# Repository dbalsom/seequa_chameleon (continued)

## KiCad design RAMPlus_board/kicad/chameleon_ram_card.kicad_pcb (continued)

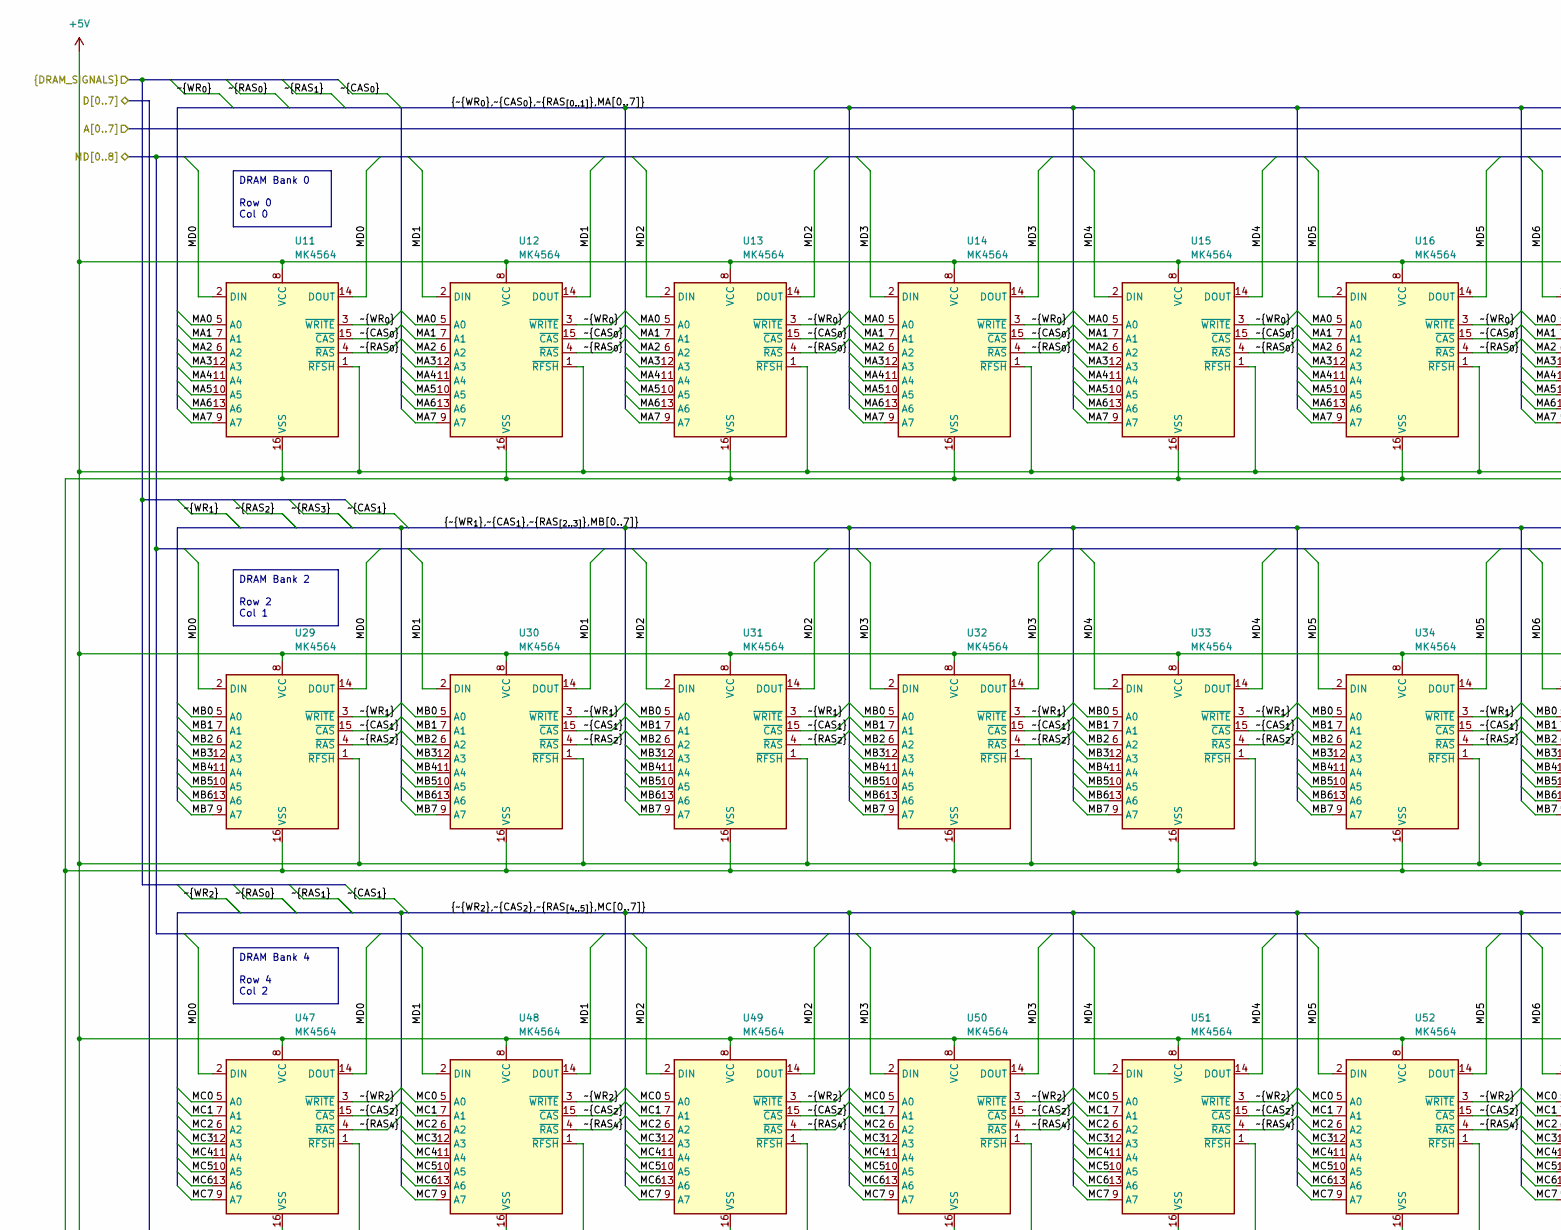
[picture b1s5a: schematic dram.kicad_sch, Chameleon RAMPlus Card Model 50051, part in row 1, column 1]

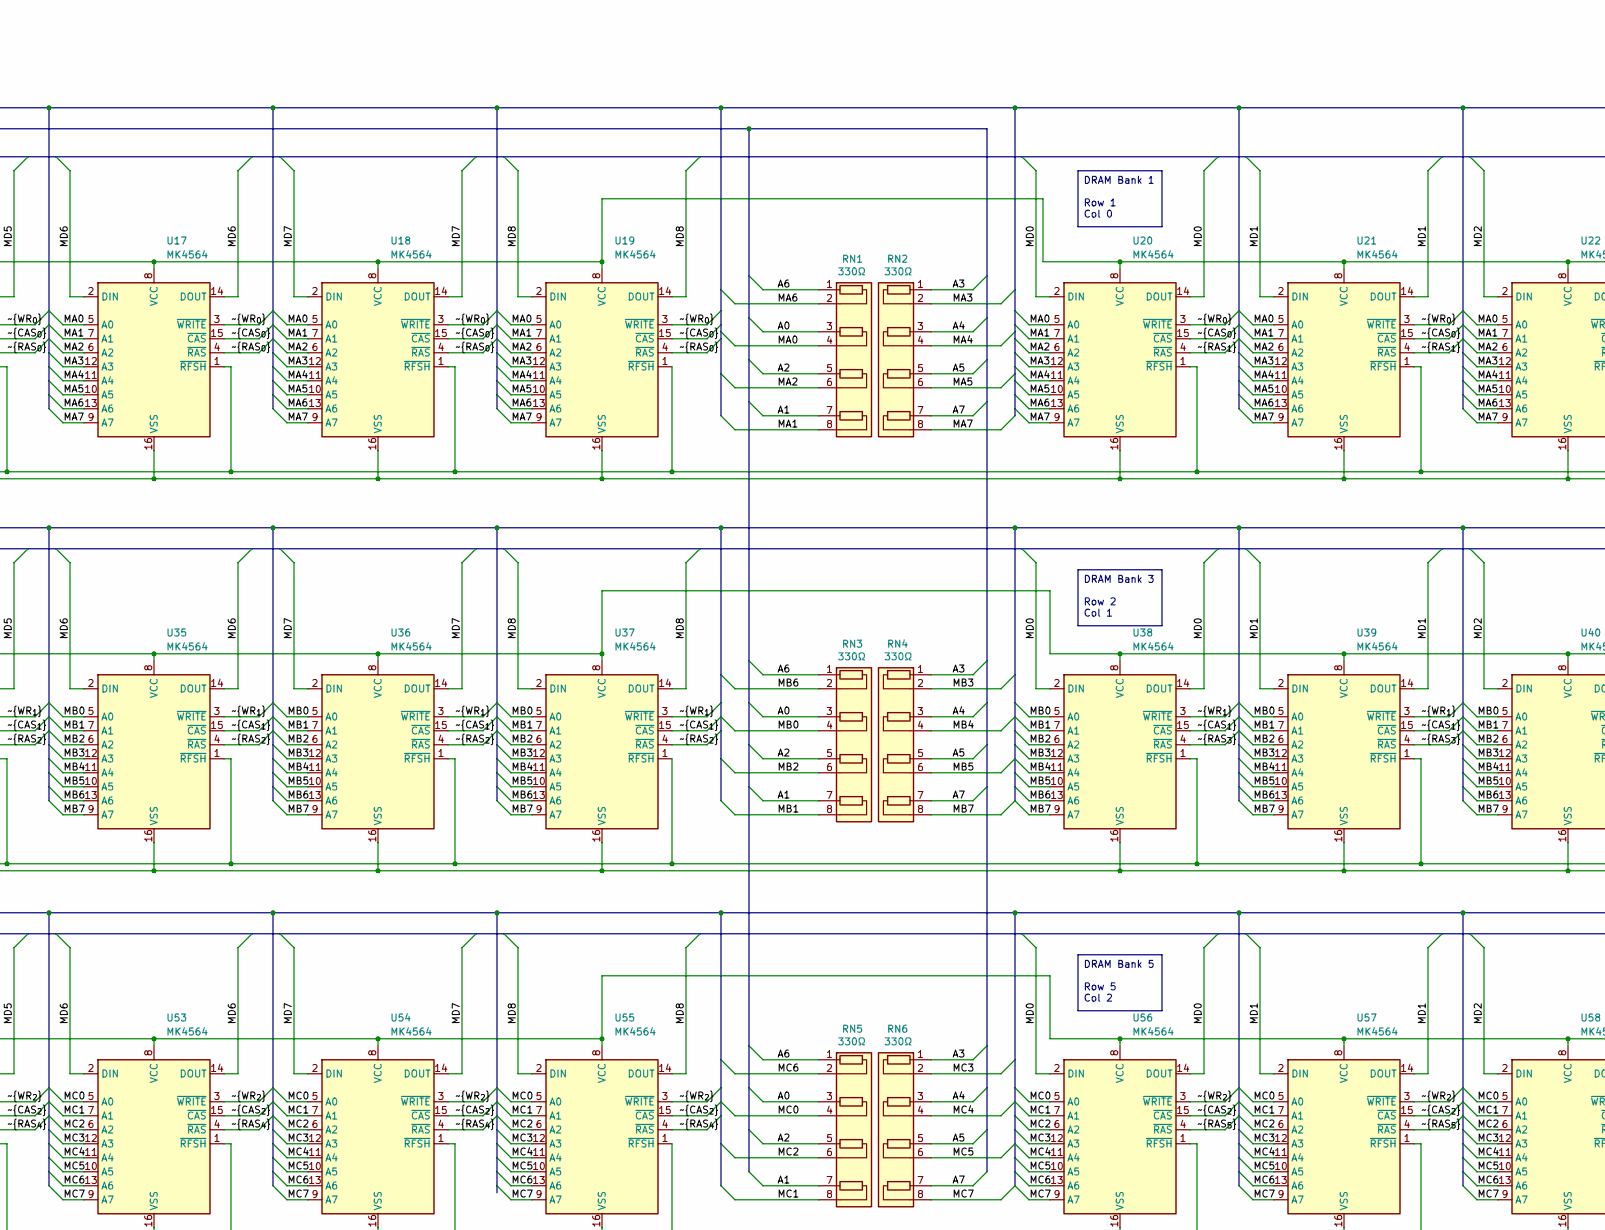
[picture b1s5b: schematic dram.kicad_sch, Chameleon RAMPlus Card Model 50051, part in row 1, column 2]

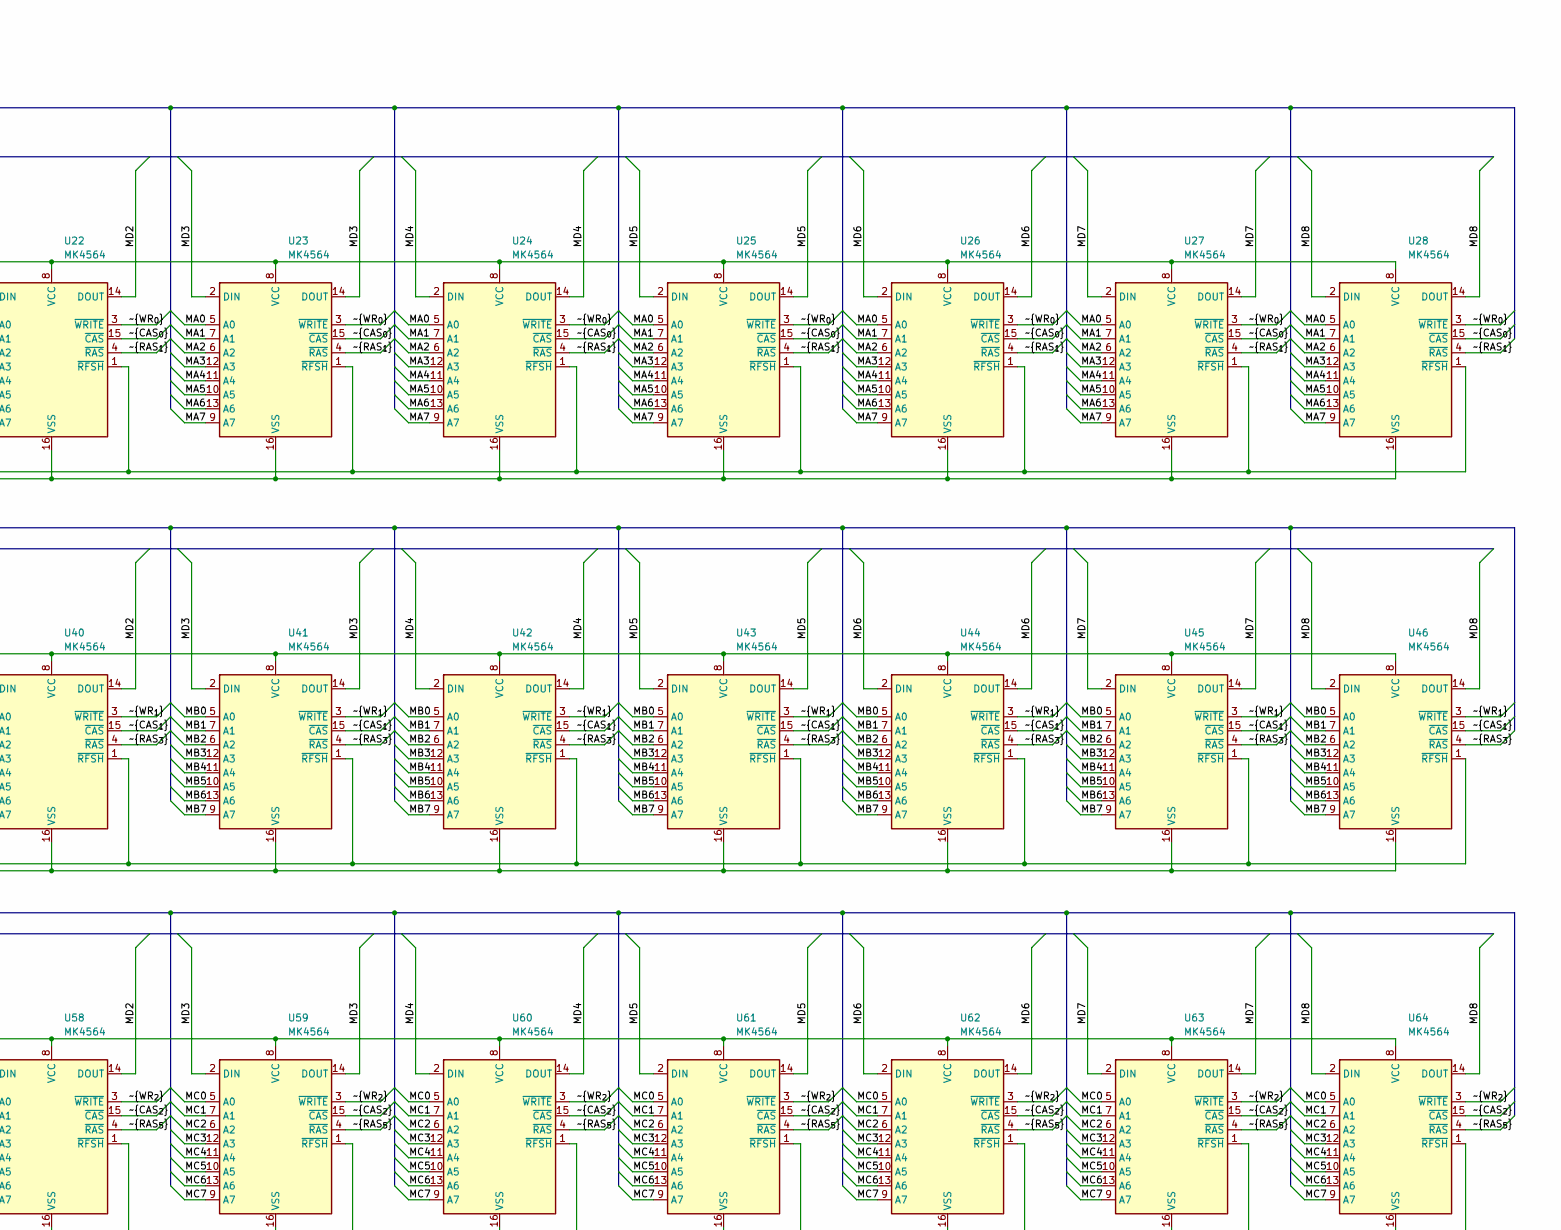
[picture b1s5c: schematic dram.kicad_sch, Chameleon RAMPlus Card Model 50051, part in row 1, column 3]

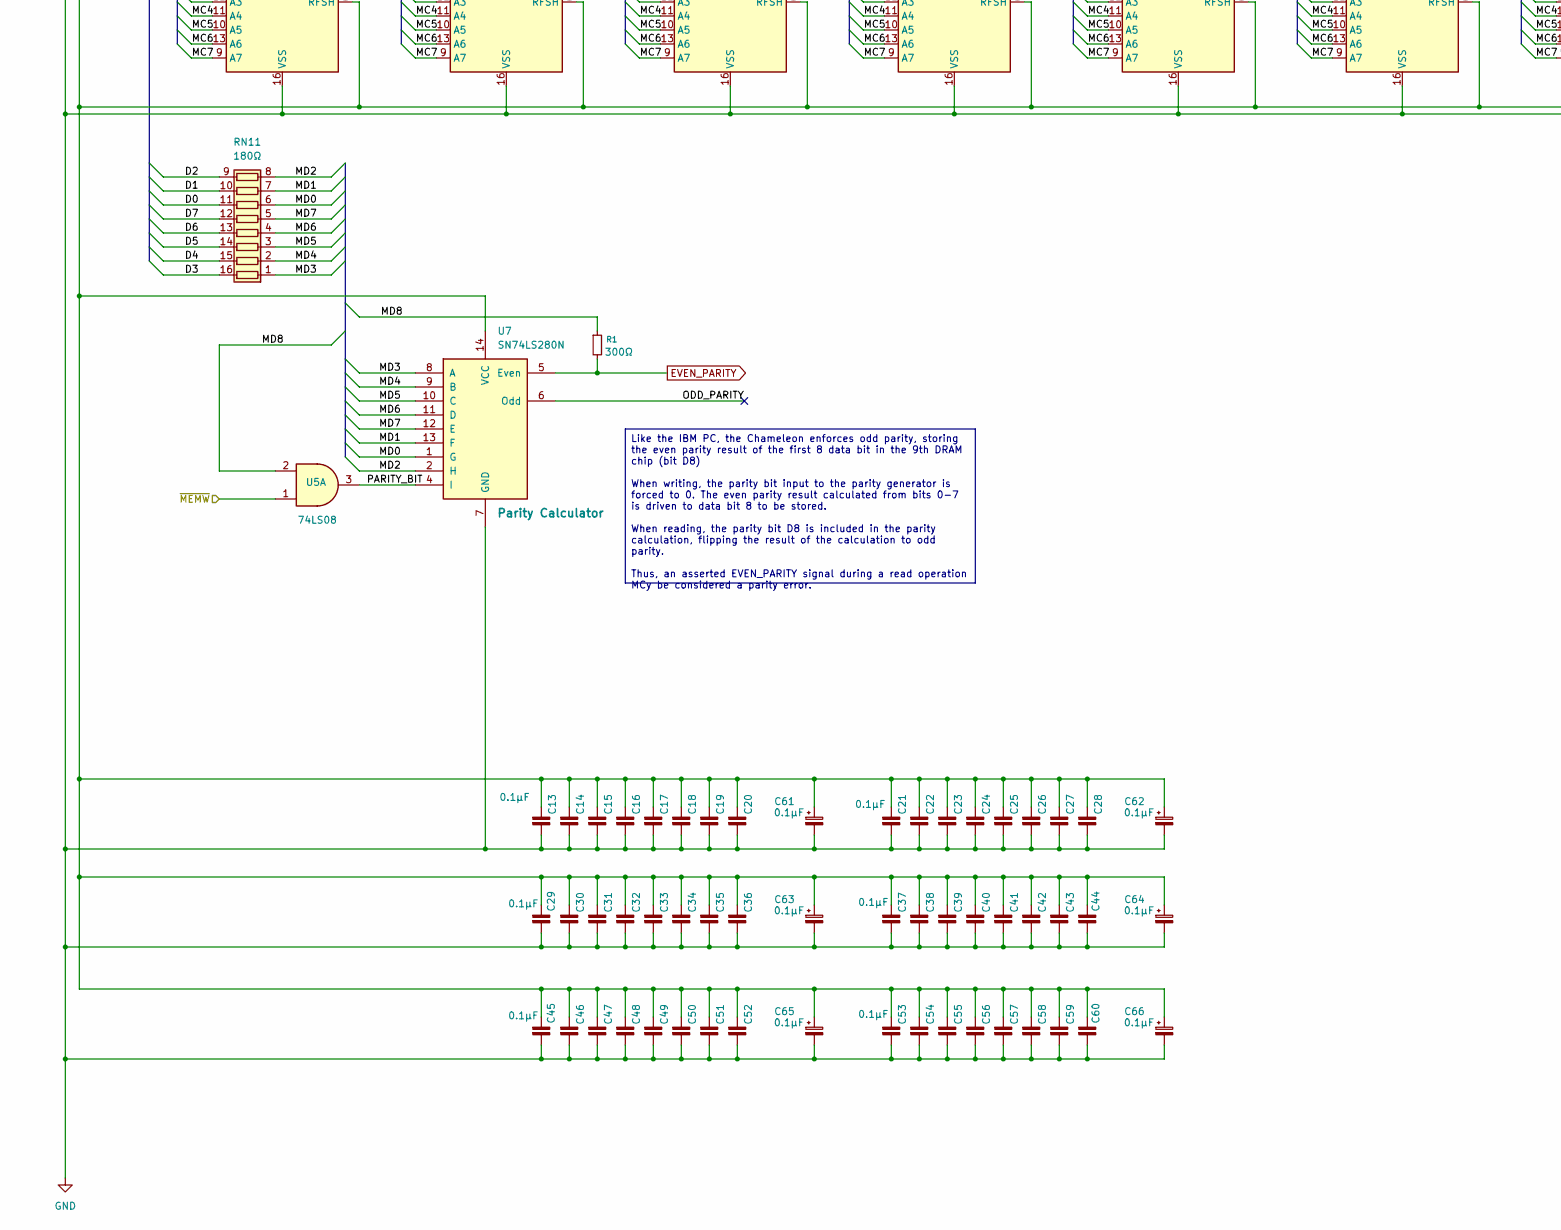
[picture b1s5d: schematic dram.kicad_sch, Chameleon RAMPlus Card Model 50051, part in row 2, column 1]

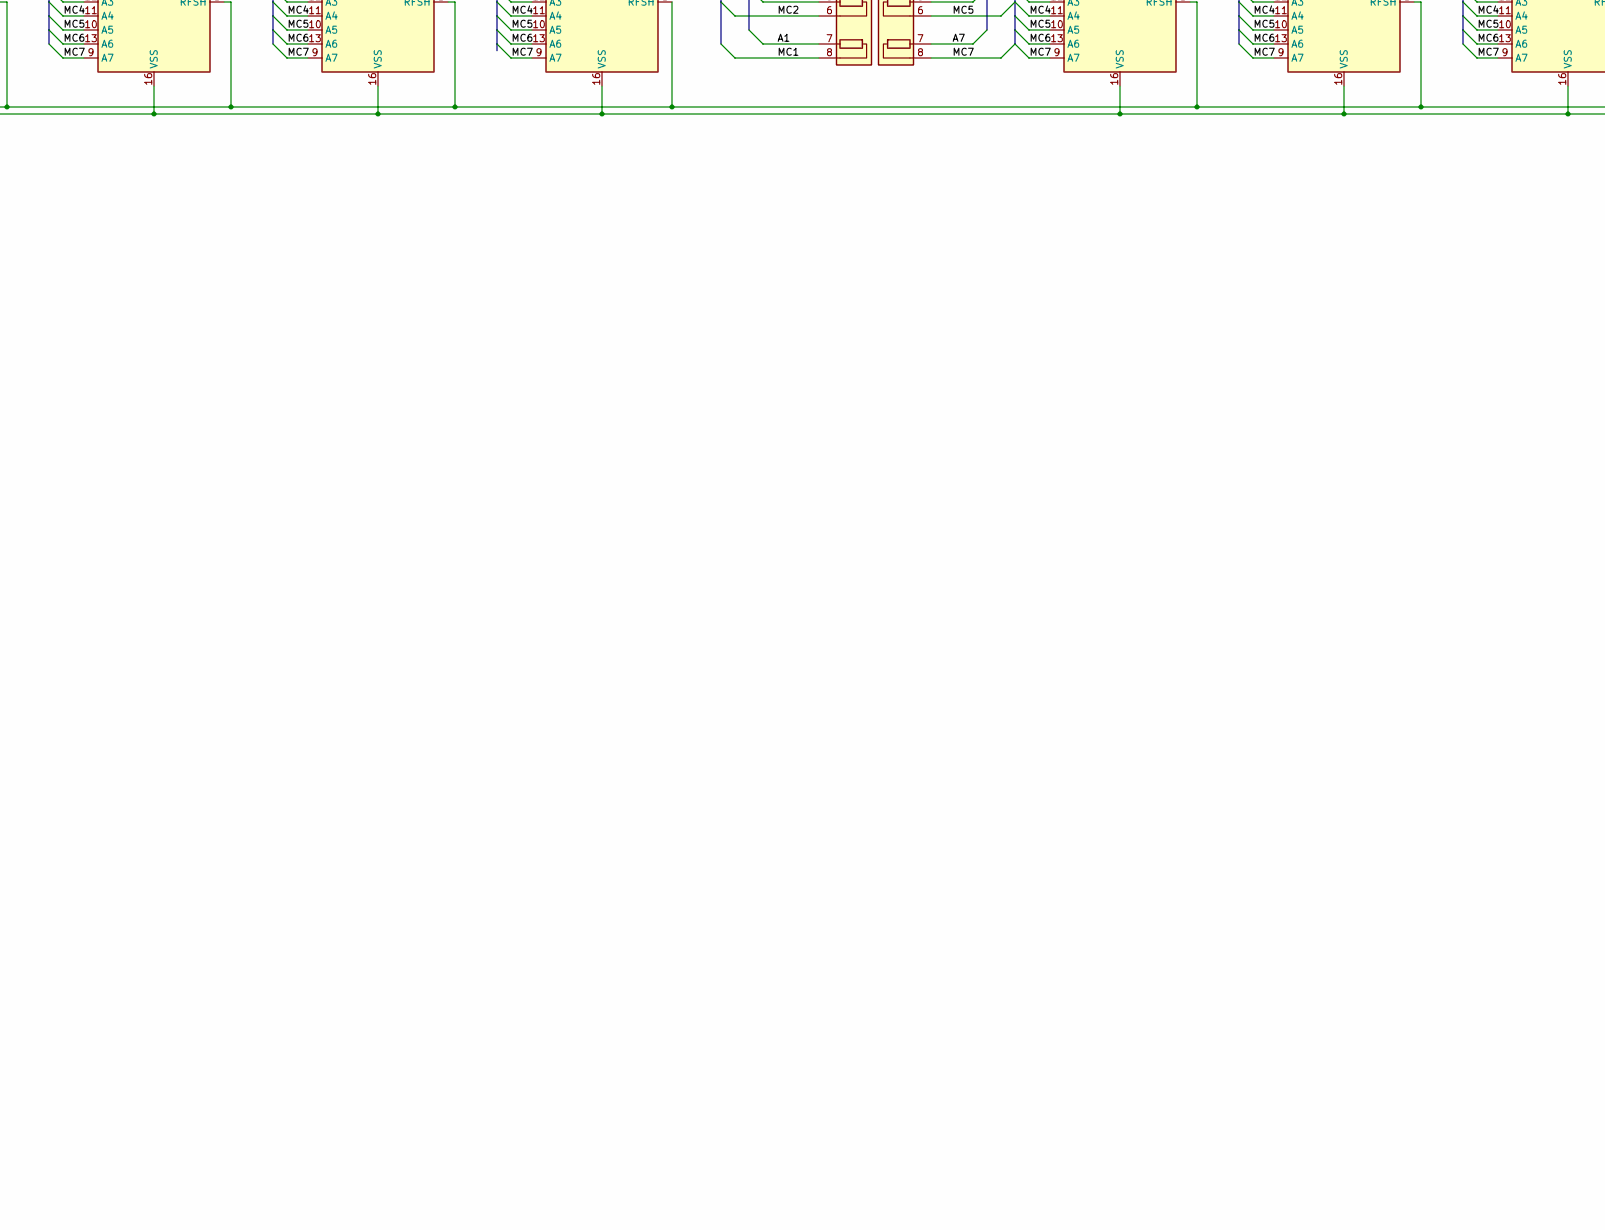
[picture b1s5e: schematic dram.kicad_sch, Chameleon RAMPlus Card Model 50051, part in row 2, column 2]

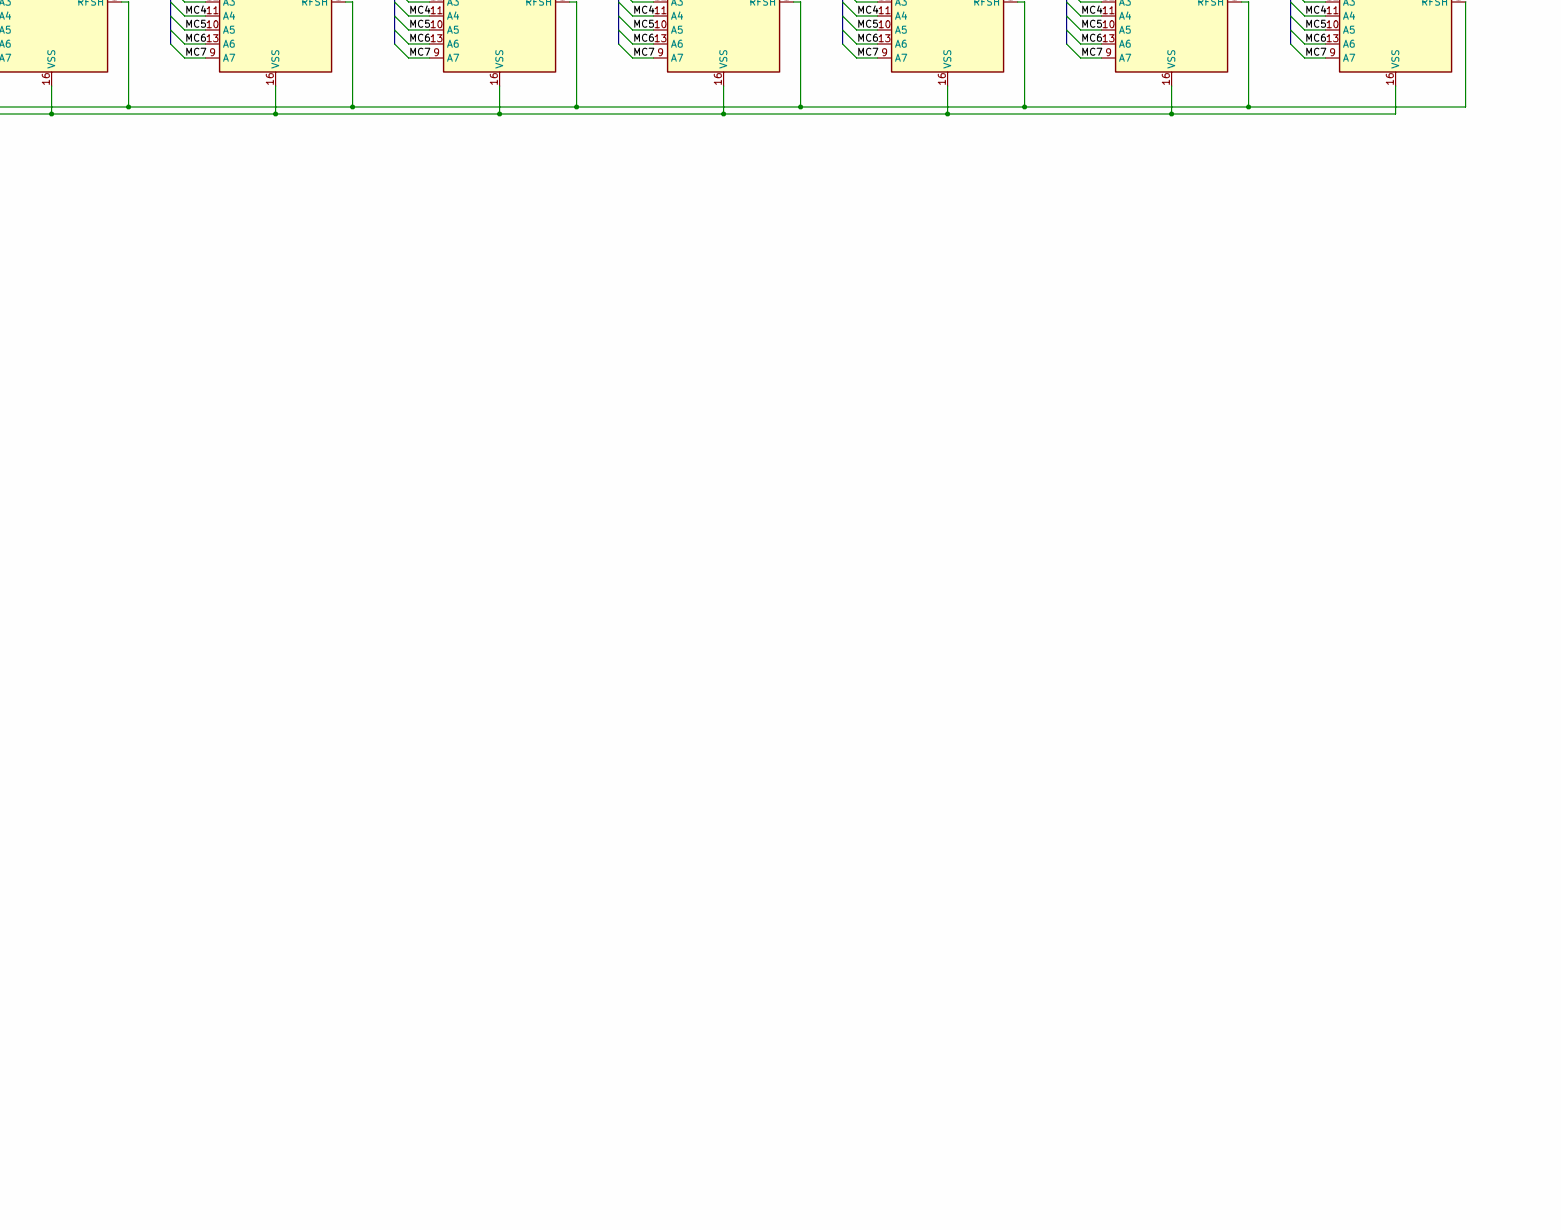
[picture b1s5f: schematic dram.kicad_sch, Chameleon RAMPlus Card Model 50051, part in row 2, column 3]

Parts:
C13, C28: 0.1µF; C_Seequa_MLCC_Bypass_P3.7mm
C14, C15, C16, C17, C18, C19, C20, C21, C22, C23, C24, C25, C26, C27, C29, C30, C31, C32, C33, C34, C35, C36, C38, C39, C40, C41, C42, C43, C44, C45, C46, C47, C48, C49, C50, C51, C52, C54, C55, C56, C57, C58, C59, C60: 0.1µF; C_Seequa_MLCC_Bypass_P7.62mm
C37, C53: 0.1µF; C_Seequa_MLCC_Bypass_P5mm
C61, C62, C63, C64, C65, C66: 0.1µF; C_Seequa_Bypass_2.54mm
R1: 300Ω; R_Seequa_P10_7.5mm_Box
RN1, RN2, RN3, RN4, RN5, RN6: 330Ω; R_Array_SIP8
RN11: 180Ω; DIP-16_W7.62mm_Socket
U5: 74LS08; DIP-14_W7.62mm_Socket
U7: SN74LS280N; DIP-14_W7.62mm_Socket
U11, U12, U13, U14, U15, U16, U17, U18, U19, U20, U21, U22, U23, U24, U25, U26, U27, U28, U29, U30, U31, U32, U33, U34, U35, U36, U37, U38, U39, U40, U41, U42, U43, U44, U45, U46, U47, U48, U49, U50, U51, U52, U53, U54, U55, U56, U57, U58, U59, U60, U61, U62, U63, U64: MK4564; DIP-16_W7.62mm_MK4164N_Socketed_With_Chip

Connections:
+5V: C13.1, C14.1, C15.1, C16.1, C17.1, C18.1, C19.1, C20.1, C21.1, C22.1, C23.1, C24.1, C25.1, C26.1, C27.1, C28.1, C29.1, C30.1, C31.1, C32.1, C33.1, C34.1, C35.1, C36.1, C37.1, C38.1, C39.1, C40.1, C41.1, C42.1, C43.1, C44.1, C45.1, C46.1, C47.1, C48.1, C49.1, C50.1, C51.1, C52.1, C53.1, C54.1, C55.1, C56.1, C57.1, C58.1, C59.1, C60.1, C61.1, C62.1, C63.1, C64.1, C65.1, C66.1, U7.14 (VCC), U11.1 (~RFSH), U11.8 (VCC), U12.1 (~RFSH), U12.8 (VCC), U13.1 (~RFSH), U13.8 (VCC), U14.1 (~RFSH), U14.8 (VCC), U15.1 (~RFSH), U15.8 (VCC), U16.1 (~RFSH), U16.8 (VCC), U17.1 (~RFSH), U17.8 (VCC), U18.1 (~RFSH), U18.8 (VCC), U19.1 (~RFSH), U19.8 (VCC), U20.1 (~RFSH), U20.8 (VCC), U21.1 (~RFSH), U21.8 (VCC), U22.1 (~RFSH), U22.8 (VCC), U23.1 (~RFSH), U23.8 (VCC), U24.1 (~RFSH), U24.8 (VCC), U25.1 (~RFSH), U25.8 (VCC), U26.1 (~RFSH), U26.8 (VCC), U27.1 (~RFSH), U27.8 (VCC), U28.1 (~RFSH), U28.8 (VCC), U29.1 (~RFSH), U29.8 (VCC), U30.1 (~RFSH), U30.8 (VCC), U31.1 (~RFSH), U31.8 (VCC), U32.1 (~RFSH), U32.8 (VCC), U33.1 (~RFSH), U33.8 (VCC), U34.1 (~RFSH), U34.8 (VCC), U35.1 (~RFSH), U35.8 (VCC), U36.1 (~RFSH), U36.8 (VCC), U37.1 (~RFSH), U37.8 (VCC), U38.1 (~RFSH), U38.8 (VCC), U39.1 (~RFSH), U39.8 (VCC), U40.1 (~RFSH), U40.8 (VCC), U41.1 (~RFSH), U41.8 (VCC), U42.1 (~RFSH), U42.8 (VCC), U43.1 (~RFSH), U43.8 (VCC), U44.1 (~RFSH), U44.8 (VCC), U45.1 (~RFSH), U45.8 (VCC), U46.1 (~RFSH), U46.8 (VCC), U47.1 (~RFSH), U47.8 (VCC), U48.1 (~RFSH), U48.8 (VCC), U49.1 (~RFSH), U49.8 (VCC), U50.1 (~RFSH), U50.8 (VCC), U51.1 (~RFSH), U51.8 (VCC), U52.1 (~RFSH), U52.8 (VCC), U53.1 (~RFSH), U53.8 (VCC), U54.1 (~RFSH), U54.8 (VCC), U55.1 (~RFSH), U55.8 (VCC), U56.1 (~RFSH), U56.8 (VCC), U57.1 (~RFSH), U57.8 (VCC), U58.1 (~RFSH), U58.8 (VCC), U59.1 (~RFSH), U59.8 (VCC), U60.1 (~RFSH), U60.8 (VCC), U61.1 (~RFSH), U61.8 (VCC), U62.1 (~RFSH), U62.8 (VCC), U63.1 (~RFSH), U63.8 (VCC), U64.1 (~RFSH), U64.8 (VCC); also elsewhere on the board
/Bus Interface & DRAM Controller/A0: RN1.3 (R2.1), RN3.3 (R2.1), RN5.3 (R2.1); also elsewhere on the board
/Bus Interface & DRAM Controller/A1: RN1.7 (R4.1), RN3.7 (R4.1), RN5.7 (R4.1); also elsewhere on the board
/Bus Interface & DRAM Controller/A2: RN1.5 (R3.1), RN3.5 (R3.1), RN5.5 (R3.1); also elsewhere on the board
/Bus Interface & DRAM Controller/A3: RN2.1 (R1.1), RN4.1 (R1.1), RN6.1 (R1.1); also elsewhere on the board
/Bus Interface & DRAM Controller/A4: RN2.3 (R2.1), RN4.3 (R2.1), RN6.3 (R2.1); also elsewhere on the board
/Bus Interface & DRAM Controller/A5: RN2.5 (R3.1), RN4.5 (R3.1), RN6.5 (R3.1); also elsewhere on the board
/Bus Interface & DRAM Controller/A6: RN1.1 (R1.1), RN3.1 (R1.1), RN5.1 (R1.1); also elsewhere on the board
/Bus Interface & DRAM Controller/A7: RN2.7 (R4.1), RN4.7 (R4.1), RN6.7 (R4.1); also elsewhere on the board
/Bus Interface & DRAM Controller/D0: RN11.11 (R6.2); also elsewhere on the board
/Bus Interface & DRAM Controller/D1: RN11.10 (R7.2); also elsewhere on the board
/Bus Interface & DRAM Controller/D2: RN11.9 (R8.2); also elsewhere on the board
/Bus Interface & DRAM Controller/D3: RN11.16 (R1.2); also elsewhere on the board
/Bus Interface & DRAM Controller/D4: RN11.15 (R2.2); also elsewhere on the board
/Bus Interface & DRAM Controller/D5: RN11.14 (R3.2); also elsewhere on the board
/Bus Interface & DRAM Controller/D6: RN11.13 (R4.2); also elsewhere on the board
/Bus Interface & DRAM Controller/D7: RN11.12 (R5.2); also elsewhere on the board
/Bus Interface & DRAM Controller/~CAS_{0}: U11.15 (~CAS), U12.15 (~CAS), U13.15 (~CAS), U14.15 (~CAS), U15.15 (~CAS), U16.15 (~CAS), U17.15 (~CAS), U18.15 (~CAS), U19.15 (~CAS), U20.15 (~CAS), U21.15 (~CAS), U22.15 (~CAS), U23.15 (~CAS), U24.15 (~CAS), U25.15 (~CAS), U26.15 (~CAS), U27.15 (~CAS), U28.15 (~CAS); also elsewhere on the board
/Bus Interface & DRAM Controller/~CAS_{1}: U29.15 (~CAS), U30.15 (~CAS), U31.15 (~CAS), U32.15 (~CAS), U33.15 (~CAS), U34.15 (~CAS), U35.15 (~CAS), U36.15 (~CAS), U37.15 (~CAS), U38.15 (~CAS), U39.15 (~CAS), U40.15 (~CAS), U41.15 (~CAS), U42.15 (~CAS), U43.15 (~CAS), U44.15 (~CAS), U45.15 (~CAS), U46.15 (~CAS); also elsewhere on the board
/Bus Interface & DRAM Controller/~CAS_{2}: U47.15 (~CAS), U48.15 (~CAS), U49.15 (~CAS), U50.15 (~CAS), U51.15 (~CAS), U52.15 (~CAS), U53.15 (~CAS), U54.15 (~CAS), U55.15 (~CAS), U56.15 (~CAS), U57.15 (~CAS), U58.15 (~CAS), U59.15 (~CAS), U60.15 (~CAS), U61.15 (~CAS), U62.15 (~CAS), U63.15 (~CAS), U64.15 (~CAS); also elsewhere on the board
/Bus Interface & DRAM Controller/~MEMW: U5.1; also elsewhere on the board
/Bus Interface & DRAM Controller/~RAS_{0}: U11.4 (~RAS), U12.4 (~RAS), U13.4 (~RAS), U14.4 (~RAS), U15.4 (~RAS), U16.4 (~RAS), U17.4 (~RAS), U18.4 (~RAS), U19.4 (~RAS); also elsewhere on the board
/Bus Interface & DRAM Controller/~RAS_{1}: U20.4 (~RAS), U21.4 (~RAS), U22.4 (~RAS), U23.4 (~RAS), U24.4 (~RAS), U25.4 (~RAS), U26.4 (~RAS), U27.4 (~RAS), U28.4 (~RAS); also elsewhere on the board
/Bus Interface & DRAM Controller/~RAS_{2}: U29.4 (~RAS), U30.4 (~RAS), U31.4 (~RAS), U32.4 (~RAS), U33.4 (~RAS), U34.4 (~RAS), U35.4 (~RAS), U36.4 (~RAS), U37.4 (~RAS); also elsewhere on the board
/Bus Interface & DRAM Controller/~RAS_{3}: U38.4 (~RAS), U39.4 (~RAS), U40.4 (~RAS), U41.4 (~RAS), U42.4 (~RAS), U43.4 (~RAS), U44.4 (~RAS), U45.4 (~RAS), U46.4 (~RAS); also elsewhere on the board
/Bus Interface & DRAM Controller/~RAS_{4}: U47.4 (~RAS), U48.4 (~RAS), U49.4 (~RAS), U50.4 (~RAS), U51.4 (~RAS), U52.4 (~RAS), U53.4 (~RAS), U54.4 (~RAS), U55.4 (~RAS); also elsewhere on the board
/Bus Interface & DRAM Controller/~RAS_{5}: U56.4 (~RAS), U57.4 (~RAS), U58.4 (~RAS), U59.4 (~RAS), U60.4 (~RAS), U61.4 (~RAS), U62.4 (~RAS), U63.4 (~RAS), U64.4 (~RAS); also elsewhere on the board
/Bus Interface & DRAM Controller/~WR_{0}: U11.3 (~WRITE), U12.3 (~WRITE), U13.3 (~WRITE), U14.3 (~WRITE), U15.3 (~WRITE), U16.3 (~WRITE), U17.3 (~WRITE), U18.3 (~WRITE), U19.3 (~WRITE), U20.3 (~WRITE), U21.3 (~WRITE), U22.3 (~WRITE), U23.3 (~WRITE), U24.3 (~WRITE), U25.3 (~WRITE), U26.3 (~WRITE), U27.3 (~WRITE), U28.3 (~WRITE); also elsewhere on the board
/Bus Interface & DRAM Controller/~WR_{1}: U29.3 (~WRITE), U30.3 (~WRITE), U31.3 (~WRITE), U32.3 (~WRITE), U33.3 (~WRITE), U34.3 (~WRITE), U35.3 (~WRITE), U36.3 (~WRITE), U37.3 (~WRITE), U38.3 (~WRITE), U39.3 (~WRITE), U40.3 (~WRITE), U41.3 (~WRITE), U42.3 (~WRITE), U43.3 (~WRITE), U44.3 (~WRITE), U45.3 (~WRITE), U46.3 (~WRITE); also elsewhere on the board
/Bus Interface & DRAM Controller/~WR_{2}: U47.3 (~WRITE), U48.3 (~WRITE), U49.3 (~WRITE), U50.3 (~WRITE), U51.3 (~WRITE), U52.3 (~WRITE), U53.3 (~WRITE), U54.3 (~WRITE), U55.3 (~WRITE), U56.3 (~WRITE), U57.3 (~WRITE), U58.3 (~WRITE), U59.3 (~WRITE), U60.3 (~WRITE), U61.3 (~WRITE), U62.3 (~WRITE), U63.3 (~WRITE), U64.3 (~WRITE); also elsewhere on the board
/DRAM Banks/MA0: RN1.4 (R2.2), U11.5 (A0), U12.5 (A0), U13.5 (A0), U14.5 (A0), U15.5 (A0), U16.5 (A0), U17.5 (A0), U18.5 (A0), U19.5 (A0), U20.5 (A0), U21.5 (A0), U22.5 (A0), U23.5 (A0), U24.5 (A0), U25.5 (A0), U26.5 (A0), U27.5 (A0), U28.5 (A0)
/DRAM Banks/MA1: RN1.8 (R4.2), U11.7 (A1), U12.7 (A1), U13.7 (A1), U14.7 (A1), U15.7 (A1), U16.7 (A1), U17.7 (A1), U18.7 (A1), U19.7 (A1), U20.7 (A1), U21.7 (A1), U22.7 (A1), U23.7 (A1), U24.7 (A1), U25.7 (A1), U26.7 (A1), U27.7 (A1), U28.7 (A1)
/DRAM Banks/MA2: RN1.6 (R3.2), U11.6 (A2), U12.6 (A2), U13.6 (A2), U14.6 (A2), U15.6 (A2), U16.6 (A2), U17.6 (A2), U18.6 (A2), U19.6 (A2), U20.6 (A2), U21.6 (A2), U22.6 (A2), U23.6 (A2), U24.6 (A2), U25.6 (A2), U26.6 (A2), U27.6 (A2), U28.6 (A2)
/DRAM Banks/MA3: RN2.2 (R1.2), U11.12 (A3), U12.12 (A3), U13.12 (A3), U14.12 (A3), U15.12 (A3), U16.12 (A3), U17.12 (A3), U18.12 (A3), U19.12 (A3), U20.12 (A3), U21.12 (A3), U22.12 (A3), U23.12 (A3), U24.12 (A3), U25.12 (A3), U26.12 (A3), U27.12 (A3), U28.12 (A3)
/DRAM Banks/MA4: RN2.4 (R2.2), U11.11 (A4), U12.11 (A4), U13.11 (A4), U14.11 (A4), U15.11 (A4), U16.11 (A4), U17.11 (A4), U18.11 (A4), U19.11 (A4), U20.11 (A4), U21.11 (A4), U22.11 (A4), U23.11 (A4), U24.11 (A4), U25.11 (A4), U26.11 (A4), U27.11 (A4), U28.11 (A4)
/DRAM Banks/MA5: RN2.6 (R3.2), U11.10 (A5), U12.10 (A5), U13.10 (A5), U14.10 (A5), U15.10 (A5), U16.10 (A5), U17.10 (A5), U18.10 (A5), U19.10 (A5), U20.10 (A5), U21.10 (A5), U22.10 (A5), U23.10 (A5), U24.10 (A5), U25.10 (A5), U26.10 (A5), U27.10 (A5), U28.10 (A5)
/DRAM Banks/MA6: RN1.2 (R1.2), U11.13 (A6), U12.13 (A6), U13.13 (A6), U14.13 (A6), U15.13 (A6), U16.13 (A6), U17.13 (A6), U18.13 (A6), U19.13 (A6), U20.13 (A6), U21.13 (A6), U22.13 (A6), U23.13 (A6), U24.13 (A6), U25.13 (A6), U26.13 (A6), U27.13 (A6), U28.13 (A6)
/DRAM Banks/MA7: RN2.8 (R4.2), U11.9 (A7), U12.9 (A7), U13.9 (A7), U14.9 (A7), U15.9 (A7), U16.9 (A7), U17.9 (A7), U18.9 (A7), U19.9 (A7), U20.9 (A7), U21.9 (A7), U22.9 (A7), U23.9 (A7), U24.9 (A7), U25.9 (A7), U26.9 (A7), U27.9 (A7), U28.9 (A7)
/DRAM Banks/MB0: RN3.4 (R2.2), U29.5 (A0), U30.5 (A0), U31.5 (A0), U32.5 (A0), U33.5 (A0), U34.5 (A0), U35.5 (A0), U36.5 (A0), U37.5 (A0), U38.5 (A0), U39.5 (A0), U40.5 (A0), U41.5 (A0), U42.5 (A0), U43.5 (A0), U44.5 (A0), U45.5 (A0), U46.5 (A0)
/DRAM Banks/MB1: RN3.8 (R4.2), U29.7 (A1), U30.7 (A1), U31.7 (A1), U32.7 (A1), U33.7 (A1), U34.7 (A1), U35.7 (A1), U36.7 (A1), U37.7 (A1), U38.7 (A1), U39.7 (A1), U40.7 (A1), U41.7 (A1), U42.7 (A1), U43.7 (A1), U44.7 (A1), U45.7 (A1), U46.7 (A1)
/DRAM Banks/MB2: RN3.6 (R3.2), U29.6 (A2), U30.6 (A2), U31.6 (A2), U32.6 (A2), U33.6 (A2), U34.6 (A2), U35.6 (A2), U36.6 (A2), U37.6 (A2), U38.6 (A2), U39.6 (A2), U40.6 (A2), U41.6 (A2), U42.6 (A2), U43.6 (A2), U44.6 (A2), U45.6 (A2), U46.6 (A2)
/DRAM Banks/MB3: RN4.2 (R1.2), U29.12 (A3), U30.12 (A3), U31.12 (A3), U32.12 (A3), U33.12 (A3), U34.12 (A3), U35.12 (A3), U36.12 (A3), U37.12 (A3), U38.12 (A3), U39.12 (A3), U40.12 (A3), U41.12 (A3), U42.12 (A3), U43.12 (A3), U44.12 (A3), U45.12 (A3), U46.12 (A3)
/DRAM Banks/MB4: RN4.4 (R2.2), U29.11 (A4), U30.11 (A4), U31.11 (A4), U32.11 (A4), U33.11 (A4), U34.11 (A4), U35.11 (A4), U36.11 (A4), U37.11 (A4), U38.11 (A4), U39.11 (A4), U40.11 (A4), U41.11 (A4), U42.11 (A4), U43.11 (A4), U44.11 (A4), U45.11 (A4), U46.11 (A4)
/DRAM Banks/MB5: RN4.6 (R3.2), U29.10 (A5), U30.10 (A5), U31.10 (A5), U32.10 (A5), U33.10 (A5), U34.10 (A5), U35.10 (A5), U36.10 (A5), U37.10 (A5), U38.10 (A5), U39.10 (A5), U40.10 (A5), U41.10 (A5), U42.10 (A5), U43.10 (A5), U44.10 (A5), U45.10 (A5), U46.10 (A5)
/DRAM Banks/MB6: RN3.2 (R1.2), U29.13 (A6), U30.13 (A6), U31.13 (A6), U32.13 (A6), U33.13 (A6), U34.13 (A6), U35.13 (A6), U36.13 (A6), U37.13 (A6), U38.13 (A6), U39.13 (A6), U40.13 (A6), U41.13 (A6), U42.13 (A6), U43.13 (A6), U44.13 (A6), U45.13 (A6), U46.13 (A6)
/DRAM Banks/MB7: RN4.8 (R4.2), U29.9 (A7), U30.9 (A7), U31.9 (A7), U32.9 (A7), U33.9 (A7), U34.9 (A7), U35.9 (A7), U36.9 (A7), U37.9 (A7), U38.9 (A7), U39.9 (A7), U40.9 (A7), U41.9 (A7), U42.9 (A7), U43.9 (A7), U44.9 (A7), U45.9 (A7), U46.9 (A7)
/DRAM Banks/MC0: RN5.4 (R2.2), U47.5 (A0), U48.5 (A0), U49.5 (A0), U50.5 (A0), U51.5 (A0), U52.5 (A0), U53.5 (A0), U54.5 (A0), U55.5 (A0), U56.5 (A0), U57.5 (A0), U58.5 (A0), U59.5 (A0), U60.5 (A0), U61.5 (A0), U62.5 (A0), U63.5 (A0), U64.5 (A0)
/DRAM Banks/MC1: RN5.8 (R4.2), U47.7 (A1), U48.7 (A1), U49.7 (A1), U50.7 (A1), U51.7 (A1), U52.7 (A1), U53.7 (A1), U54.7 (A1), U55.7 (A1), U56.7 (A1), U57.7 (A1), U58.7 (A1), U59.7 (A1), U60.7 (A1), U61.7 (A1), U62.7 (A1), U63.7 (A1), U64.7 (A1)
/DRAM Banks/MC2: RN5.6 (R3.2), U47.6 (A2), U48.6 (A2), U49.6 (A2), U50.6 (A2), U51.6 (A2), U52.6 (A2), U53.6 (A2), U54.6 (A2), U55.6 (A2), U56.6 (A2), U57.6 (A2), U58.6 (A2), U59.6 (A2), U60.6 (A2), U61.6 (A2), U62.6 (A2), U63.6 (A2), U64.6 (A2)
/DRAM Banks/MC3: RN6.2 (R1.2), U47.12 (A3), U48.12 (A3), U49.12 (A3), U50.12 (A3), U51.12 (A3), U52.12 (A3), U53.12 (A3), U54.12 (A3), U55.12 (A3), U56.12 (A3), U57.12 (A3), U58.12 (A3), U59.12 (A3), U60.12 (A3), U61.12 (A3), U62.12 (A3), U63.12 (A3), U64.12 (A3)
/DRAM Banks/MC4: RN6.4 (R2.2), U47.11 (A4), U48.11 (A4), U49.11 (A4), U50.11 (A4), U51.11 (A4), U52.11 (A4), U53.11 (A4), U54.11 (A4), U55.11 (A4), U56.11 (A4), U57.11 (A4), U58.11 (A4), U59.11 (A4), U60.11 (A4), U61.11 (A4), U62.11 (A4), U63.11 (A4), U64.11 (A4)
/DRAM Banks/MC5: RN6.6 (R3.2), U47.10 (A5), U48.10 (A5), U49.10 (A5), U50.10 (A5), U51.10 (A5), U52.10 (A5), U53.10 (A5), U54.10 (A5), U55.10 (A5), U56.10 (A5), U57.10 (A5), U58.10 (A5), U59.10 (A5), U60.10 (A5), U61.10 (A5), U62.10 (A5), U63.10 (A5), U64.10 (A5)
/DRAM Banks/MC6: RN5.2 (R1.2), U47.13 (A6), U48.13 (A6), U49.13 (A6), U50.13 (A6), U51.13 (A6), U52.13 (A6), U53.13 (A6), U54.13 (A6), U55.13 (A6), U56.13 (A6), U57.13 (A6), U58.13 (A6), U59.13 (A6), U60.13 (A6), U61.13 (A6), U62.13 (A6), U63.13 (A6), U64.13 (A6)
/DRAM Banks/MC7: RN6.8 (R4.2), U47.9 (A7), U48.9 (A7), U49.9 (A7), U50.9 (A7), U51.9 (A7), U52.9 (A7), U53.9 (A7), U54.9 (A7), U55.9 (A7), U56.9 (A7), U57.9 (A7), U58.9 (A7), U59.9 (A7), U60.9 (A7), U61.9 (A7), U62.9 (A7), U63.9 (A7), U64.9 (A7)
/DRAM Banks/MD0: RN11.6 (R6.1), U7.1 (G), U11.2 (DIN), U11.14 (DOUT), U20.2 (DIN), U20.14 (DOUT), U29.2 (DIN), U29.14 (DOUT), U38.2 (DIN), U38.14 (DOUT), U47.2 (DIN), U47.14 (DOUT), U56.2 (DIN), U56.14 (DOUT); also elsewhere on the board
/DRAM Banks/MD1: RN11.7 (R7.1), U7.13 (F), U12.2 (DIN), U12.14 (DOUT), U21.2 (DIN), U21.14 (DOUT), U30.2 (DIN), U30.14 (DOUT), U39.2 (DIN), U39.14 (DOUT), U48.2 (DIN), U48.14 (DOUT), U57.2 (DIN), U57.14 (DOUT); also elsewhere on the board
/DRAM Banks/MD2: RN11.8 (R8.1), U7.2 (H), U13.2 (DIN), U13.14 (DOUT), U22.2 (DIN), U22.14 (DOUT), U31.2 (DIN), U31.14 (DOUT), U40.2 (DIN), U40.14 (DOUT), U49.2 (DIN), U49.14 (DOUT), U58.2 (DIN), U58.14 (DOUT); also elsewhere on the board
/DRAM Banks/MD3: RN11.1 (R1.1), U7.8 (A), U14.2 (DIN), U14.14 (DOUT), U23.2 (DIN), U23.14 (DOUT), U32.2 (DIN), U32.14 (DOUT), U41.2 (DIN), U41.14 (DOUT), U50.2 (DIN), U50.14 (DOUT), U59.2 (DIN), U59.14 (DOUT); also elsewhere on the board
/DRAM Banks/MD4: RN11.2 (R2.1), U7.9 (B), U15.2 (DIN), U15.14 (DOUT), U24.2 (DIN), U24.14 (DOUT), U33.2 (DIN), U33.14 (DOUT), U42.2 (DIN), U42.14 (DOUT), U51.2 (DIN), U51.14 (DOUT), U60.2 (DIN), U60.14 (DOUT); also elsewhere on the board
/DRAM Banks/MD5: RN11.3 (R3.1), U7.10 (C), U16.2 (DIN), U16.14 (DOUT), U25.2 (DIN), U25.14 (DOUT), U34.2 (DIN), U34.14 (DOUT), U43.2 (DIN), U43.14 (DOUT), U52.2 (DIN), U52.14 (DOUT), U61.2 (DIN), U61.14 (DOUT); also elsewhere on the board
/DRAM Banks/MD6: RN11.4 (R4.1), U7.11 (D), U17.2 (DIN), U17.14 (DOUT), U26.2 (DIN), U26.14 (DOUT), U35.2 (DIN), U35.14 (DOUT), U44.2 (DIN), U44.14 (DOUT), U53.2 (DIN), U53.14 (DOUT), U62.2 (DIN), U62.14 (DOUT); also elsewhere on the board
/DRAM Banks/MD7: RN11.5 (R5.1), U7.12 (E), U18.2 (DIN), U18.14 (DOUT), U27.2 (DIN), U27.14 (DOUT), U36.2 (DIN), U36.14 (DOUT), U45.2 (DIN), U45.14 (DOUT), U54.2 (DIN), U54.14 (DOUT), U63.2 (DIN), U63.14 (DOUT); also elsewhere on the board
/DRAM Banks/MD8: R1.1, U5.2, U19.2 (DIN), U19.14 (DOUT), U28.2 (DIN), U28.14 (DOUT), U37.2 (DIN), U37.14 (DOUT), U46.2 (DIN), U46.14 (DOUT), U55.2 (DIN), U55.14 (DOUT), U64.2 (DIN), U64.14 (DOUT)
/DRAM Banks/ODD_PARITY: U7.6 (Odd)
/DRAM Banks/PARITY_BIT: U5.3, U7.4 (I)
EVEN_PARITY: R1.2, U7.5 (Even); also elsewhere on the board
GND: C13.2, C14.2, C15.2, C16.2, C17.2, C18.2, C19.2, C20.2, C21.2, C22.2, C23.2, C24.2, C25.2, C26.2, C27.2, C28.2, C29.2, C30.2, C31.2, C32.2, C33.2, C34.2, C35.2, C36.2, C37.2, C38.2, C39.2, C40.2, C41.2, C42.2, C43.2, C44.2, C45.2, C46.2, C47.2, C48.2, C49.2, C50.2, C51.2, C52.2, C53.2, C54.2, C55.2, C56.2, C57.2, C58.2, C59.2, C60.2, C61.2, C62.2, C63.2, C64.2, C65.2, C66.2, U7.7 (GND), U11.16 (VSS), U12.16 (VSS), U13.16 (VSS), U14.16 (VSS), U15.16 (VSS), U16.16 (VSS), U17.16 (VSS), U18.16 (VSS), U19.16 (VSS), U20.16 (VSS), U21.16 (VSS), U22.16 (VSS), U23.16 (VSS), U24.16 (VSS), U25.16 (VSS), U26.16 (VSS), U27.16 (VSS), U28.16 (VSS), U29.16 (VSS), U30.16 (VSS), U31.16 (VSS), U32.16 (VSS), U33.16 (VSS), U34.16 (VSS), U35.16 (VSS), U36.16 (VSS), U37.16 (VSS), U38.16 (VSS), U39.16 (VSS), U40.16 (VSS), U41.16 (VSS), U42.16 (VSS), U43.16 (VSS), U44.16 (VSS), U45.16 (VSS), U46.16 (VSS), U47.16 (VSS), U48.16 (VSS), U49.16 (VSS), U50.16 (VSS), U51.16 (VSS), U52.16 (VSS), U53.16 (VSS), U54.16 (VSS), U55.16 (VSS), U56.16 (VSS), U57.16 (VSS), U58.16 (VSS), U59.16 (VSS), U60.16 (VSS), U61.16 (VSS), U62.16 (VSS), U63.16 (VSS), U64.16 (VSS); also elsewhere on the board

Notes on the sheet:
DRAM Bank 4 Row 4 Col 2
Like the IBM PC, the Chameleon enforces odd parity, storing the even parity result of the first 8 data bit in the 9th DRAM chip (bit D8) When writing, the parity bit input to the parity generator is forced to 0. The even parity result calculated from bits 0-7 is driven to data bit 8 to be stored. W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
DRAM Bank 3 Row 2 Col 1
DRAM Bank 1 Row 1 Col 0
DRAM Bank 2 Row 2 Col 1
DRAM Bank 5 Row 5 Col 2
DRAM Bank 0 Row 0 Col 0
